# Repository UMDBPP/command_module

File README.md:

# ```</CMD>```

Command is the primary tracking payload flown by BPP. This repository contains design files and software required to run the current version of command.

Current POC:
Shipman

 ## Design Priciples
As the command module needs to fly on every flight mass reduction is a primary focus. For this reason a switch from perfboard to custom PCB's was done, and a substantial reduction in box volume is underway. Reliability is incredibly important and for this reason the payload operates its tracking systems in a full 4N redundant method.
### Tracking systems include (system/function):
#### 2x LiteAPRS 2m transmitters on 144.390 MHz
In flight position updates every minute. By nature of APRS tracking in hilly terrain unlikely to receive exact coordinates under 500m unless operating our own radios.
#### 1x SPOT Trace Tracker
COTS tracker from SPOT. Gives exact coordinates on landing.
#### 1x BITS (Balloon Iridium Telemetry System)
Exact coordinates throughout the flight, variable transmission rate 1min-15minutes (technically 10s-inf). Datalogger. XBee 900 HP allows for commands to be relayed through Iridium to other payloads and telemetry from payloads to be sent to ground. Possibility of ground to payload XBee communication without Iridium allowing for low latency high rate commanding.

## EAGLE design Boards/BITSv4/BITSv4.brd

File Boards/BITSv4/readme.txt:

Folder for BITSv4 development
Starting 10/3/2021,
jmolter

Work based on lessons from BITSv3

---Focus Areas---

-Reg LMR16020-
Keep the IC
Change inductor for easier assembly
Consider chaning output to 5v,
OR source 5v from another source

-Misc.-
Change power connector to match LightAPRS LVC

Change picoblade to right angle

Remove celltracker crosstalk conn

Consider GPS improvements

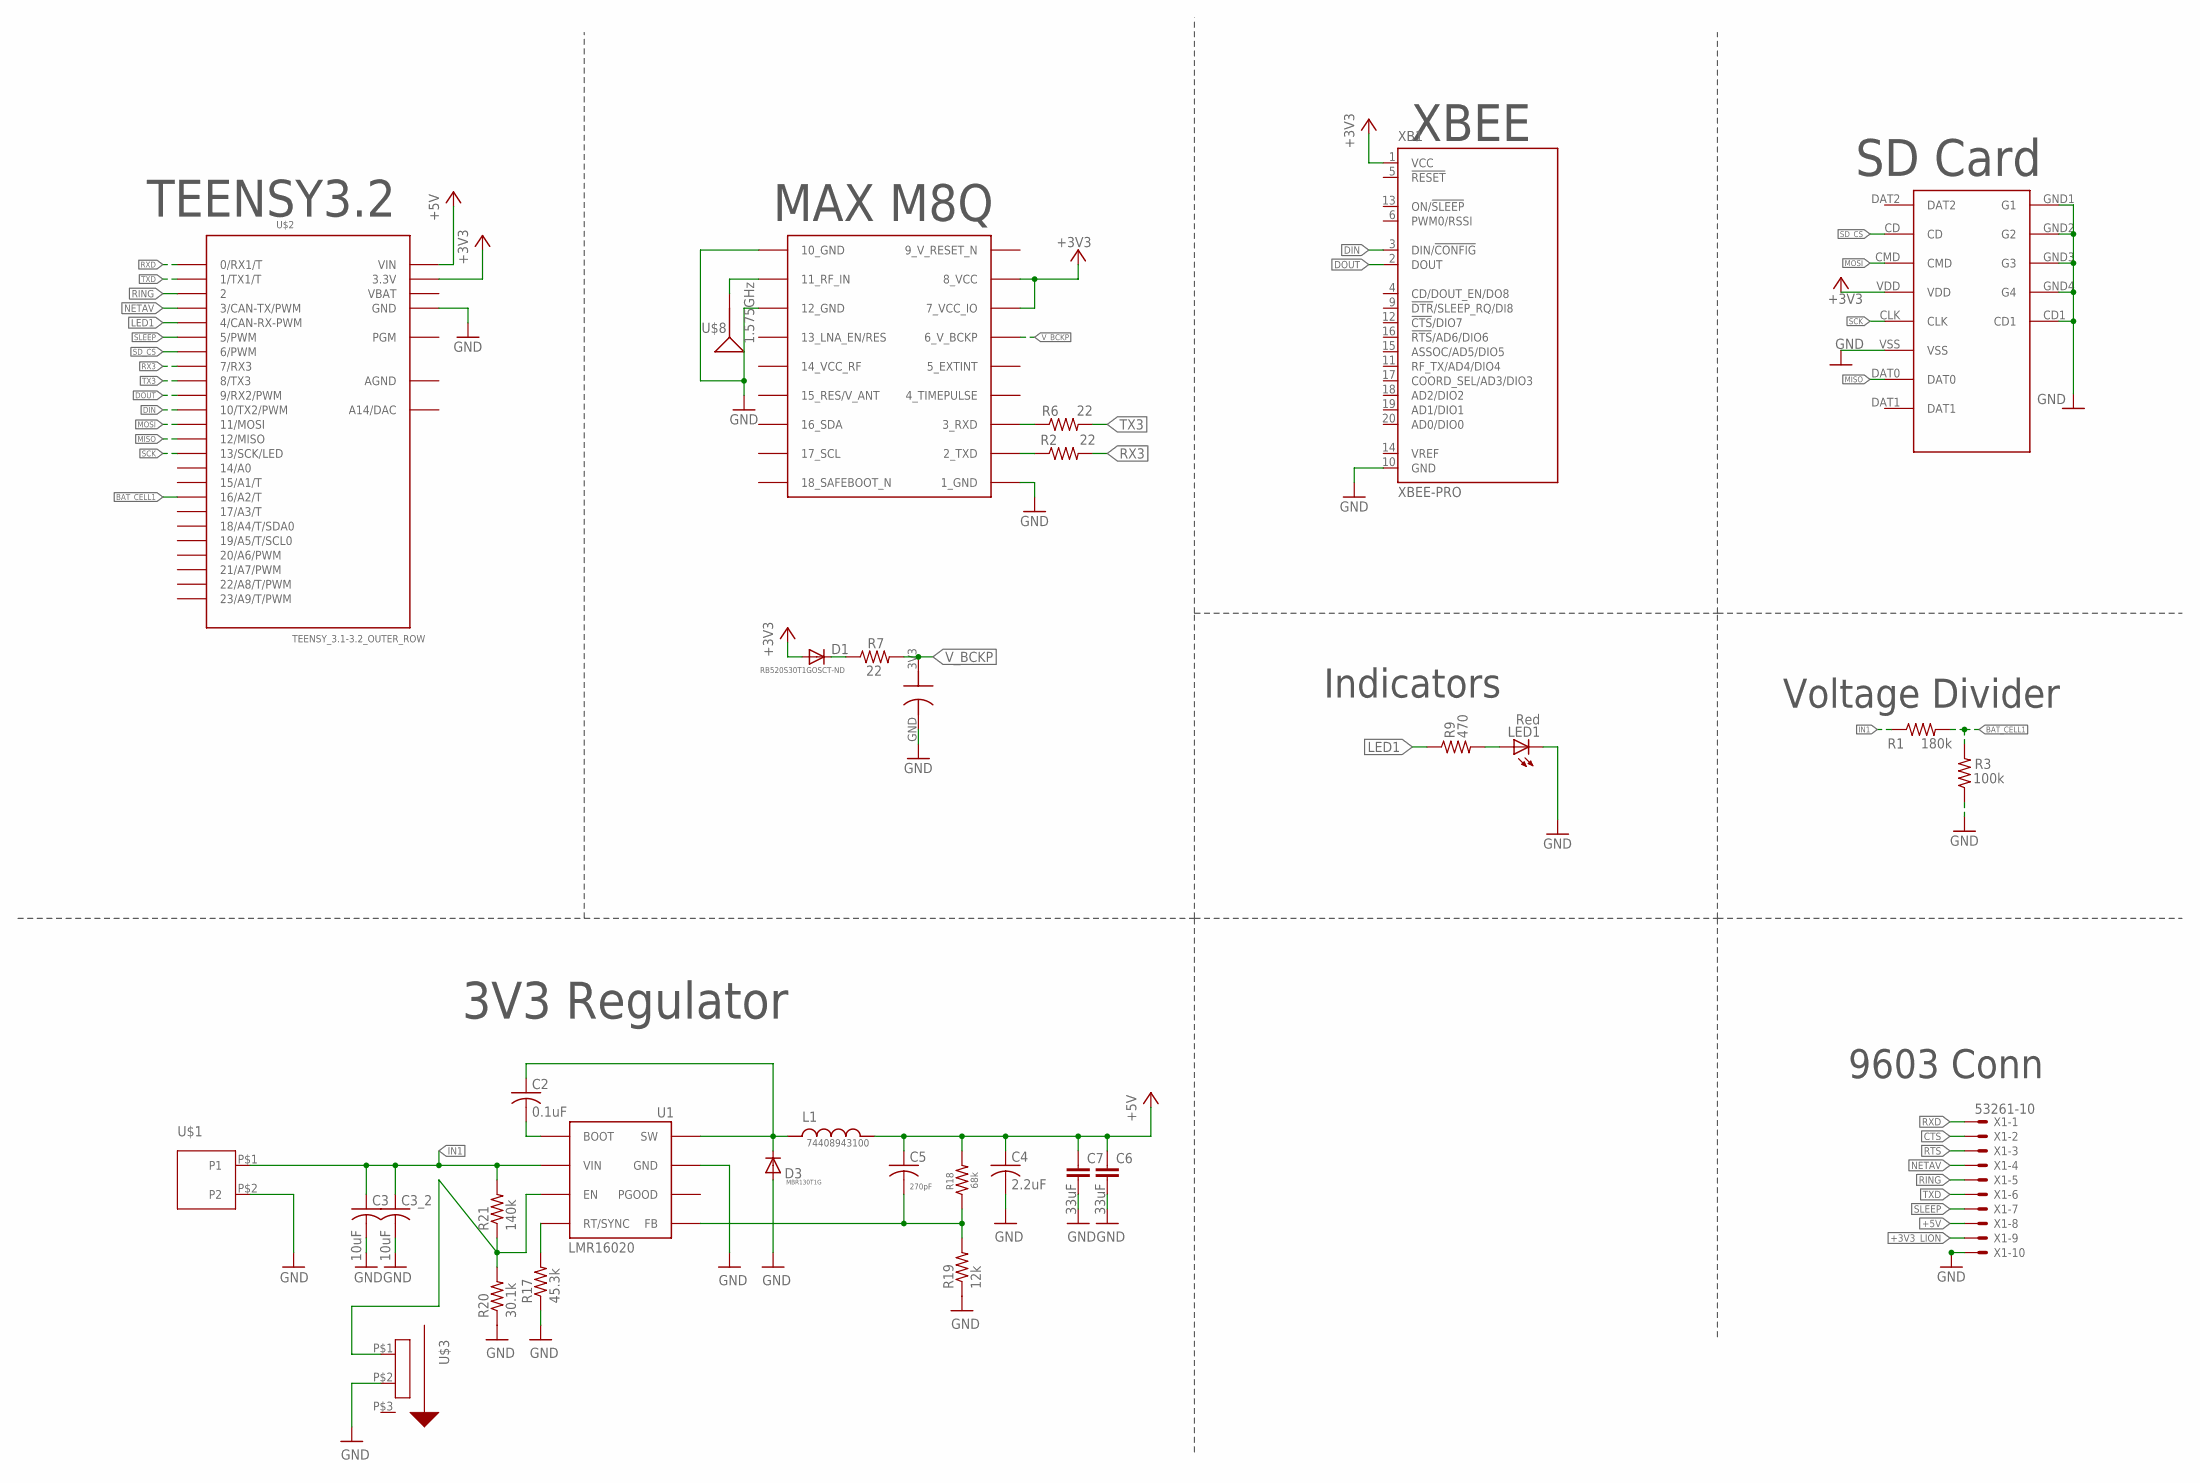
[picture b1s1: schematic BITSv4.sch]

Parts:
C1: 0.2F; ELNASUPERCAP
C2: 0.1uF; C0603
C3, C3_2: 10uF; C0805
C4: 2.2uF; C0603
C5: 270pF; C0402
C6, C7: 33uF; C050-024X044
D1: RB520S30T1GOSCT-ND; SOD523
D3: MBR130T1G; SOD-123_MINI-SMA
L1: 74408943100
LED1: Red; CHIP-LED0603
R1: 180k; R0603
R2, R6, R7: 22; R0603
R3: 100k; R0603
R9: 470; R0603
R17: 45.3k; R0603
R18: 68k; R0603
R19: 12k; R0603
R20: 30.1k; R0603
R21: 140k; R0603
U1: LMR16020; SO8
U$1: 559350210
U$2: TEENSY_3.1-3.2_OUTER_ROW; TEENSY_3.0-3.2&LC_OUTER_ROW
U$3: CL-SB-12B-01
U$4: MICRO_SD; MICRO_SD_HINGED
U$7: MAX-M8
U$8: 1.575GHz; SPARKFUN-GPS_ANT-GPS-2X7MM
X1: 53261-10
XB1: XBEE-PRO

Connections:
9_V_RESET_N: U$7.9_RESET_N (9_V_RESET_N)
+3V3: D1.A, U$2.3.3V, U$2.3.3V1 (3.3V), U$4.VDD, U$7.7_VCC_IO, U$7.8_VCC, XB1.1 (VCC)
+3V3_LION: X1.9
+5V: C4.1, C5.1, C6.1, C7.1, L1.P$2, R18.2, U$2.VIN, X1.8
AGND: U$2.AGND
BAT_CELL1: R1.2, R3.2, U$2.16/A2 (16/A2/T)
CTS: X1.2
DIN: U$2.10 (10/TX2/PWM), XB1.3 (DIN/!CONFIG)
DOUT: U$2.9 (9/RX2/PWM), XB1.2 (DOUT)
FB: C5.2, R18.1, R19.2, U1.P$5 (FB)
GND: C1.GND, C3.2, C3_2.2, C4.2, C6.2, C7.2, D3.A, LED1.C, R3.1, R17.1, R19.1, R20.1, U1.P$7 (GND), U1.PAD (GND), U$1.P$2 (P2), U$2.GND, U$2.GND1 (GND), U$3.P$2 (P2), U$4.CD1, U$4.GND1 (G1), U$4.GND2 (G2), U$4.GND3 (G3), U$4.GND4 (G4), U$4.VSS, U$7.1_GND, U$7.10_GND, U$7.12_GND, X1.10, XB1.10 (GND)
IN1: C3.1, C3_2.1, R1.1, R21.2, U1.P$2 (VIN), U$1.P$1 (P1)
LED1: R9.1, U$2.4 (4/CAN-RX-PWM)
MISO: U$2.12 (12/MISO), U$4.DAT0
MOSI: U$2.11 (11/MOSI), U$4.CMD
unnamed: U$7.11_RF_IN, U$8.1
unnamed: D1.C, R7.1
unnamed: R6.1, U$7.3_RXD
unnamed: R2.1, U$7.2_TXD
unnamed: LED1.A, R9.2
unnamed: R20.2, R21.1, U1.P$3 (EN), U$3.P$1 (P1)
unnamed: R17.2, U1.P$4 (RT/SYNC)
unnamed: C2.2, U1.P$1 (BOOT)
NETAV: U$2.3 (3/CAN-TX/PWM), X1.4
RING: U$2.2, X1.5
RTS: X1.3
RX3: R2.2, U$2.7 (7/RX3)
RXD: U$2.0 (0/RX1/T), X1.1
SCK: U$2.13 (13/SCK/LED), U$4.CLK
SD_CS: U$2.6 (6/PWM), U$4.CD
SLEEP: U$2.5 (5/PWM), X1.7
SW: C2.1, D3.C, L1.P$1, U1.P$8 (SW)
TX3: R6.2, U$2.8 (8/TX3)
TXD: U$2.1 (1/TX1/T), X1.6
VBAT: U$2.VBAT
V_BCKP: C1.3V3, R7.2, U$7.6_V_BCKP

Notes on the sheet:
MAX M8Q
TEENSY3.2
Voltage Divider
Indicators
SD Card
9603 Conn
3V3 Regulator
XBEE

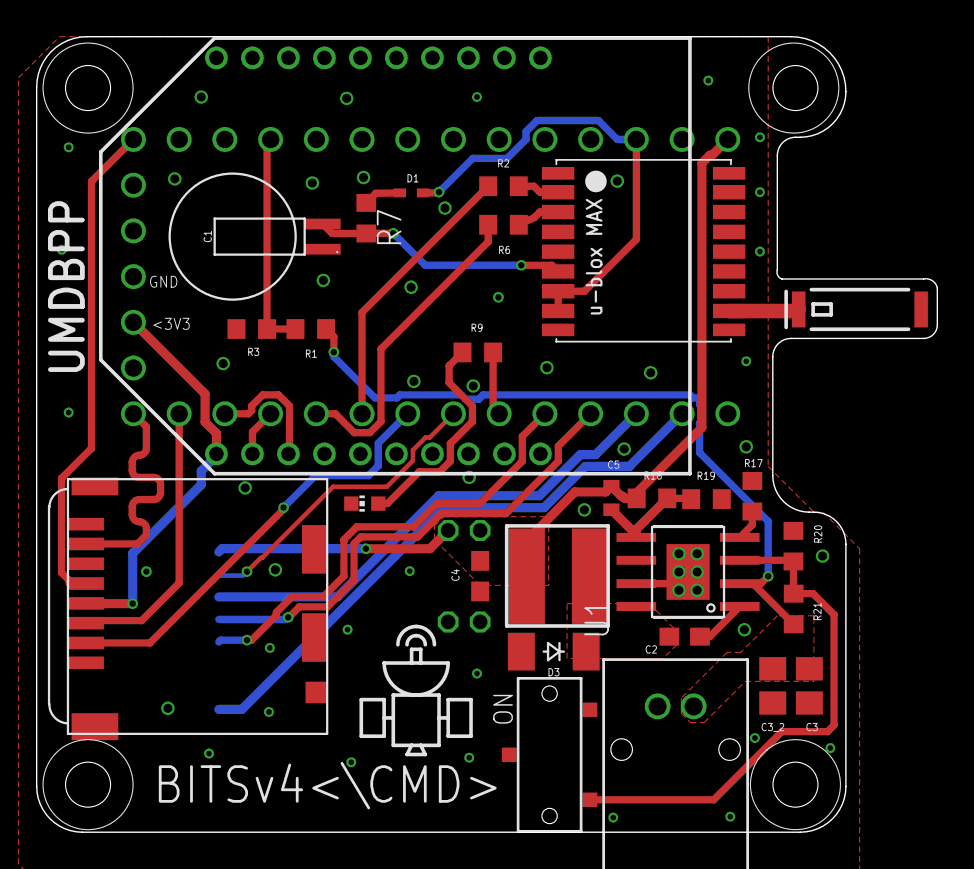
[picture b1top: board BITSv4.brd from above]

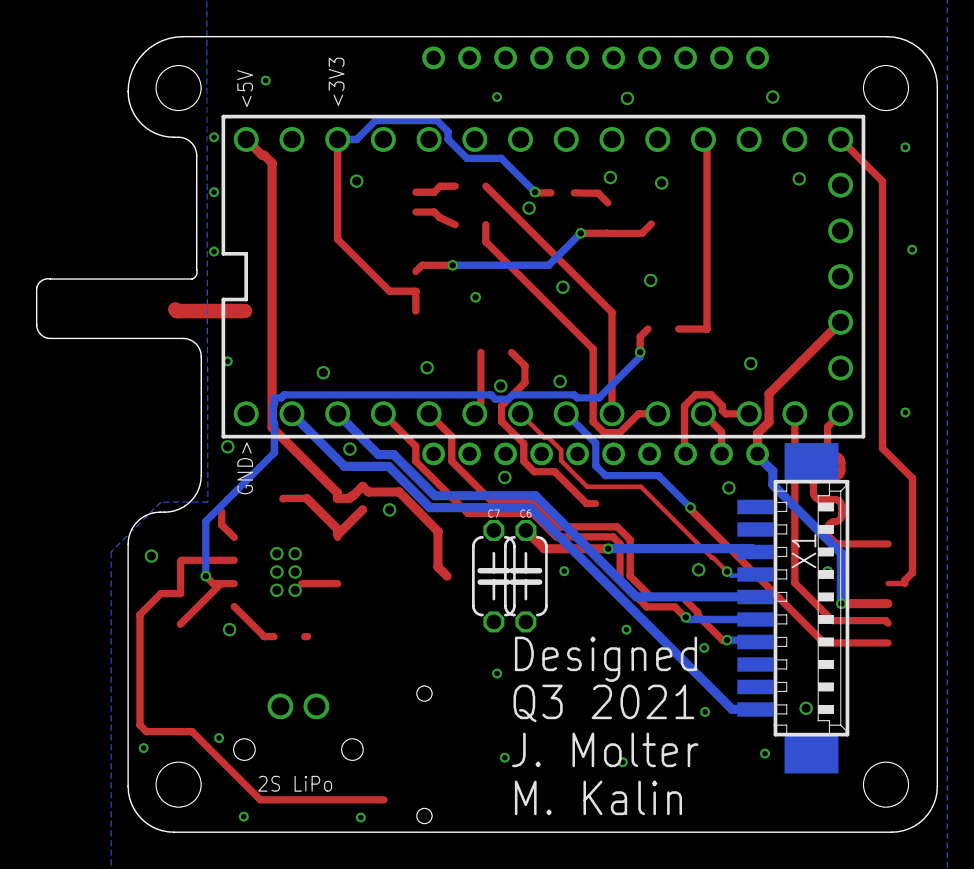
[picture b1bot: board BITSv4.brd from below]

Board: 2 copper layers, 50.0 x 44.2 mm, 32 parts (4 on the bottom side), 30 nets.

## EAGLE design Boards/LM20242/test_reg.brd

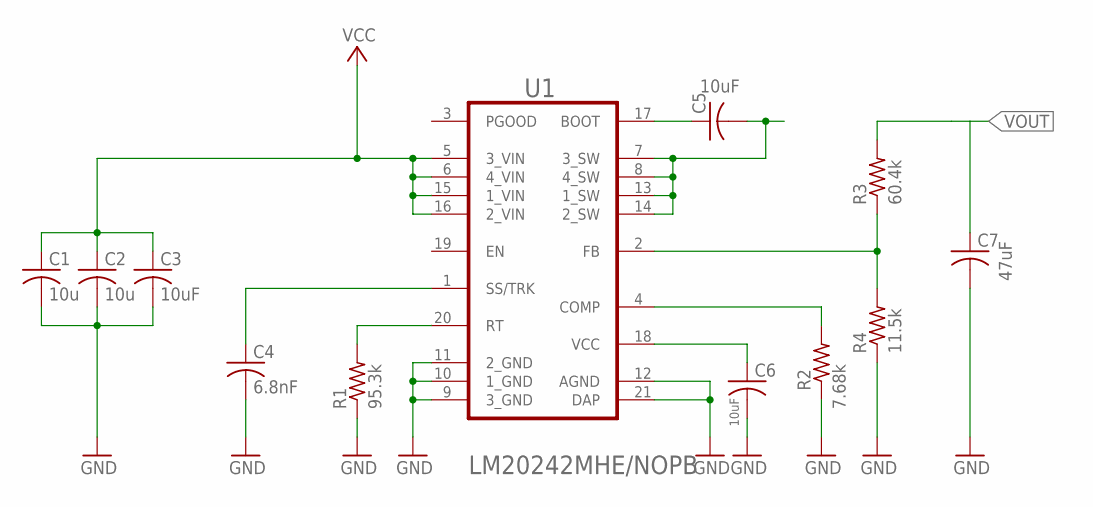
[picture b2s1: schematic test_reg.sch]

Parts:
C1, C2: 10u; C0805
C3, C5, C6: 10uF; C0805
C4: 6.8nF; C0805
C7: 47uF; C0805
R1: 95.3k; R0805
R2: 7.68k; R0805
R3: 60.4k; R0805
R4: 11.5k; R0805
U1: TI_NATIONAL_SEMICONDUCTOR_LM20242MHE-NOPBTI_NATIO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; TI_NATIONAL_SEMICONDUCTOR_LM20242MHE-NOPB_0

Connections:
GND: C1.2, C2.2, C3.2, C4.2, C6.2, C7.2, R1.1, R2.1, R4.1, U1.9 (3_GND), U1.10 (1_GND), U1.11 (2_GND), U1.12 (AGND), U1.21 (DAP)
unnamed: R1.2, U1.20 (RT)
unnamed: R2.2, U1.4 (COMP)
unnamed: C4.1, U1.1 (SS/TRK)
unnamed: C5.2, U1.7 (3_SW), U1.8 (4_SW), U1.13 (1_SW), U1.14 (2_SW)
unnamed: C5.1, U1.17 (BOOT)
unnamed: R3.1, R4.2, U1.2 (FB)
unnamed: C6.1, U1.18 (VCC)
VCC: C1.1, C2.1, C3.1, U1.5 (3_VIN), U1.6 (4_VIN), U1.15 (1_VIN), U1.16 (2_VIN)
VOUT: C7.1, R3.2

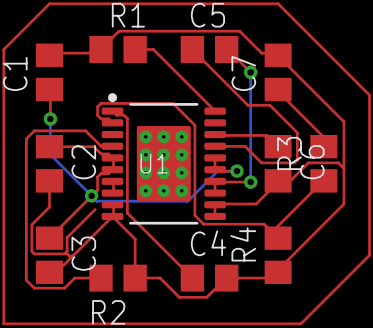
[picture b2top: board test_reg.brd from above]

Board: 2 copper layers, 12 parts (0 on the bottom side), 10 nets.

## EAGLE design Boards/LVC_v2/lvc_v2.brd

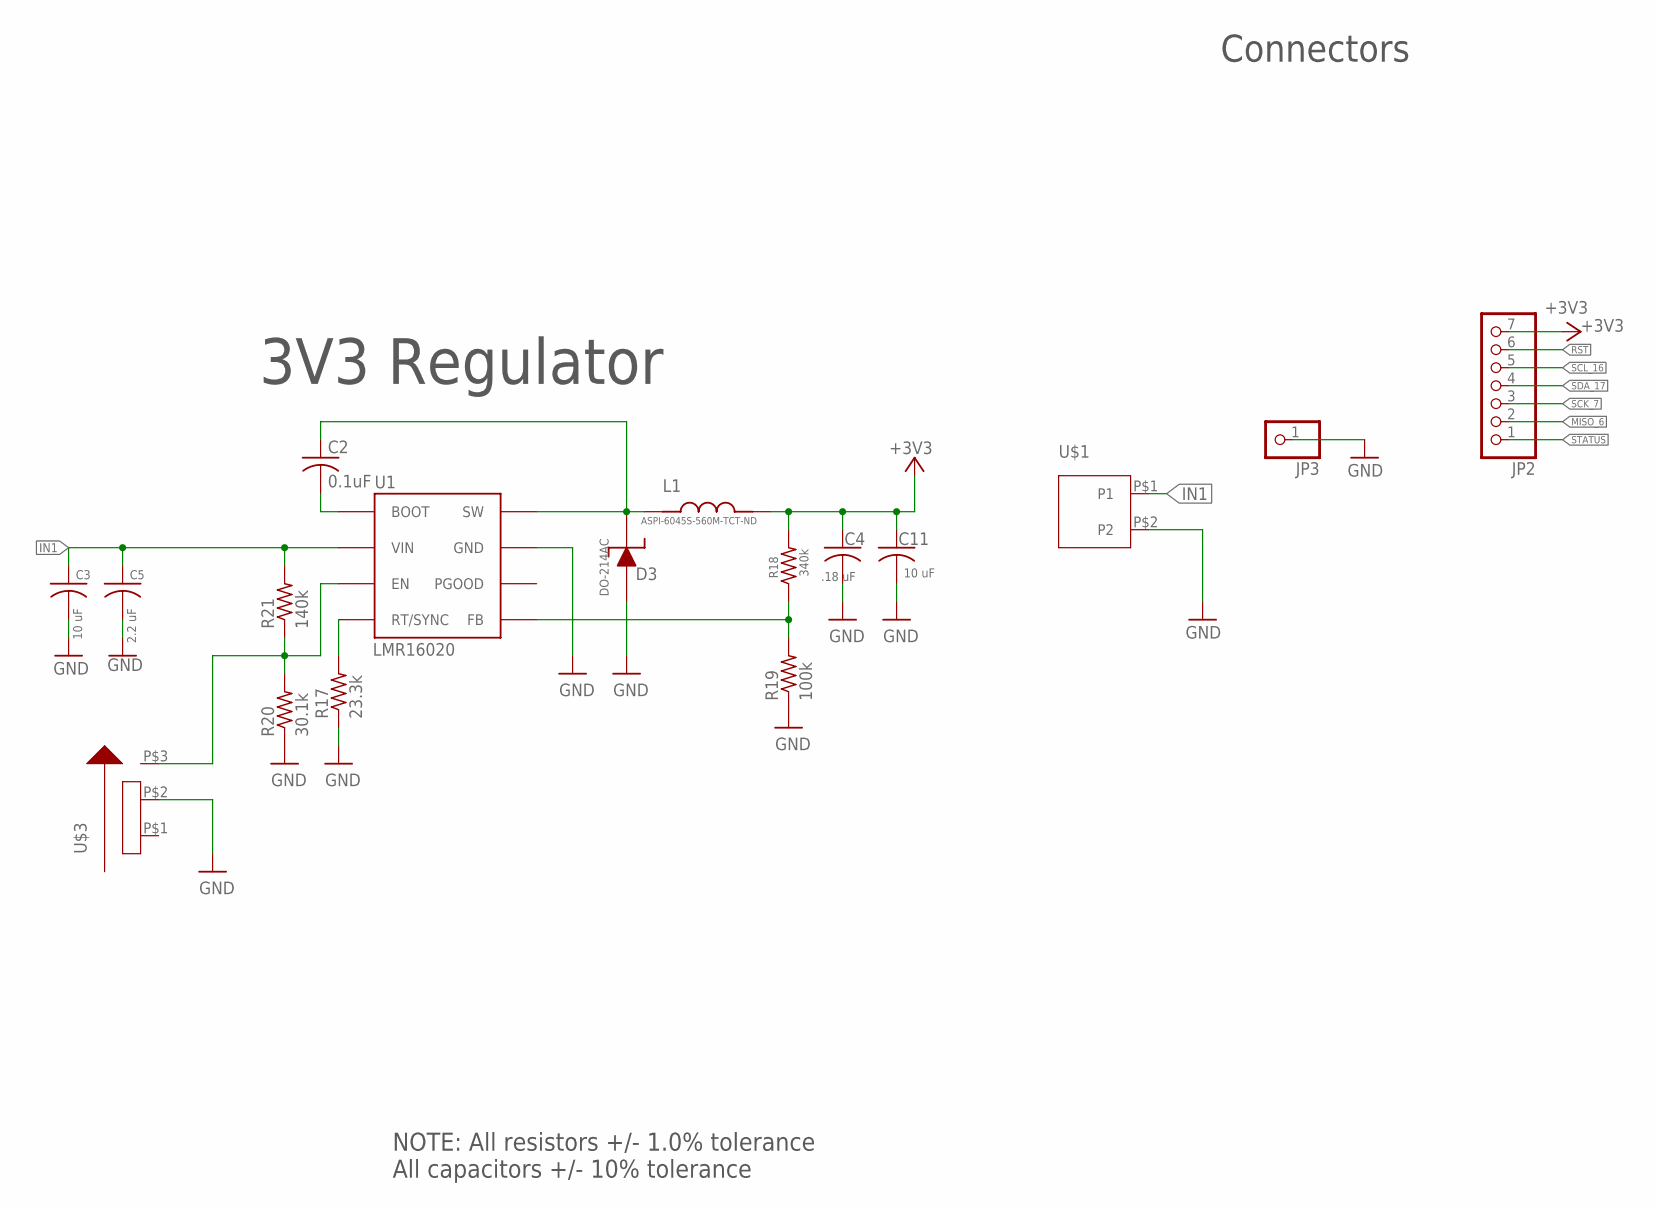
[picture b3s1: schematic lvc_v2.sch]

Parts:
C2: 0.1uF; C0603
C3: 10 uF; C1210
C4: .18 uF; C0603
C5: 2.2 uF; C1210
C11: 10 uF; C0603
D3: DO-214AC
JP2: PINHD-1X7; 1X07
JP3: PINHD-1X1; 1X01
L1: ASPI-6045S-560M-TCT-ND; ABRACON
R17: 23.3k; R0603
R18: 340k; R0603
R19: 100k; R0603
R20: 30.1k; R0603
R21: 140k; R0603
U1: LMR16020; SO8
U$1: 559350210
U$3: CL-SB-12B-01

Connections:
+3V3: C4.1, C11.1, JP2.7, L1.P$2, R18.2
FB: R18.1, R19.2, U1.P$5 (FB)
GND: C3.2, C4.2, C5.2, C11.2, D3.P$1, JP3.1, R17.1, R19.1, R20.1, U1.P$7 (GND), U1.PAD (GND), U$1.P$2 (P2), U$3.P$2 (P2)
IN1: C3.1, C5.1, R21.2, U1.P$2 (VIN), U$1.P$1 (P1)
MISO_6: JP2.2
unnamed: R20.2, R21.1, U1.P$3 (EN), U$3.P$3 (P3)
unnamed: R17.2, U1.P$4 (RT/SYNC)
unnamed: C2.2, U1.P$1 (BOOT)
RST: JP2.6
SCK_7: JP2.3
SCL_16: JP2.5
SDA_17: JP2.4
STATUS: JP2.1
SW: C2.1, D3.P$2, L1.P$1, U1.P$8 (SW)

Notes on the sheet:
Connectors
NOTE: All resistors +/- 1.0% tolerance All capacitors +/- 10% tolerance
3V3 Regulator

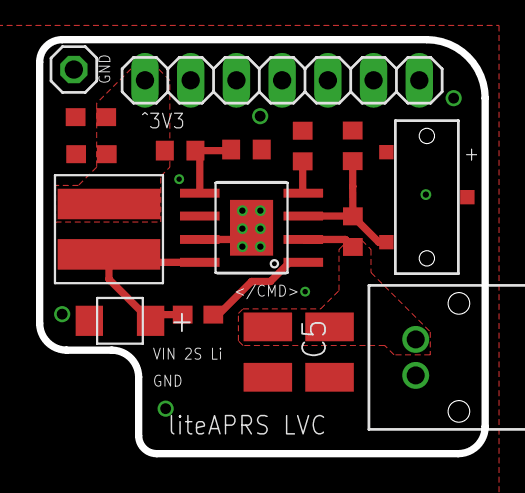
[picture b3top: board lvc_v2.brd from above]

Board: 2 copper layers, 24.8 x 23.0 mm, 17 parts (0 on the bottom side), 8 nets.

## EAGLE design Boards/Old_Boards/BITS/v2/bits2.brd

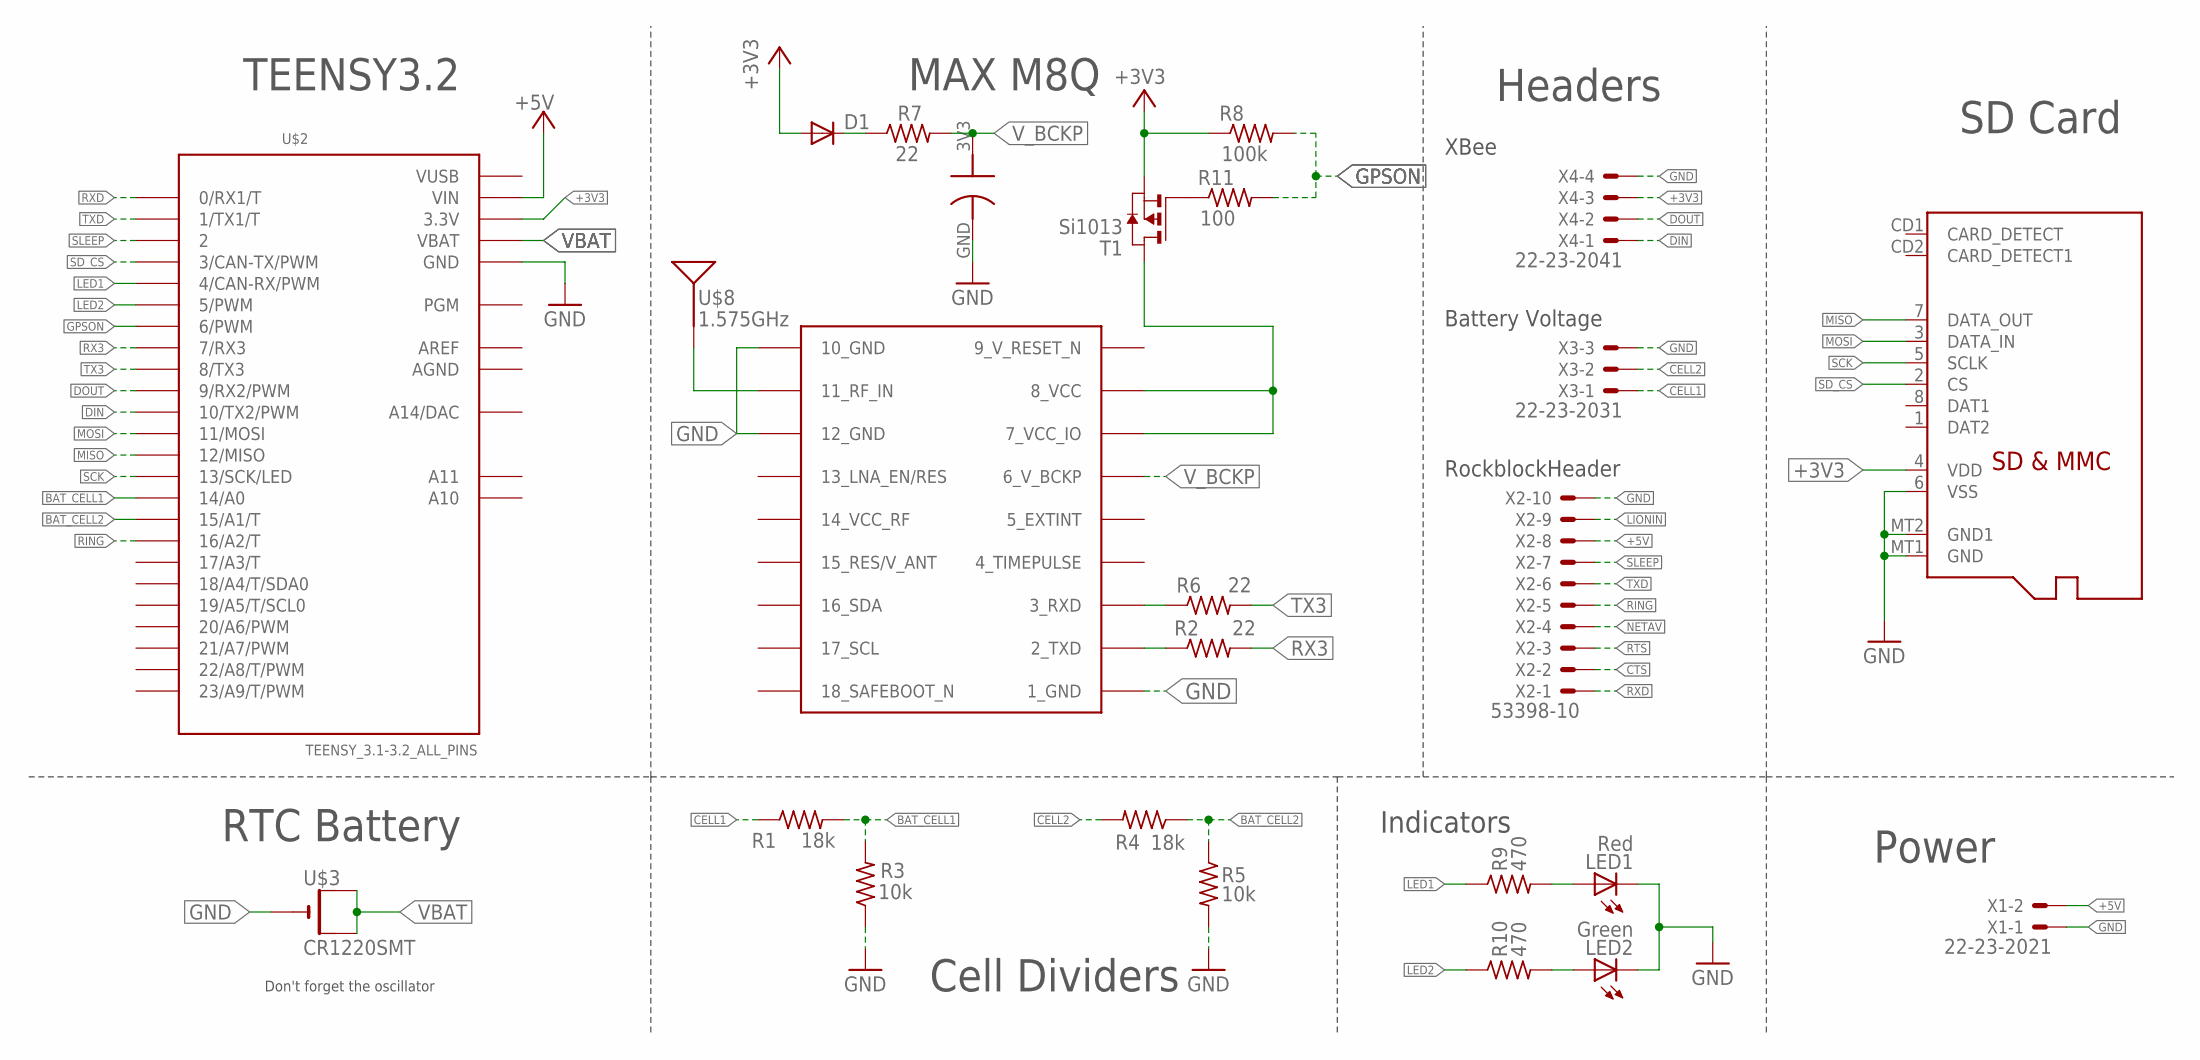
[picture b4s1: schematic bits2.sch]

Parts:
C1: DCK-3R3E204T614-E; ELNASUPERCAP
D1: DIODE-SOD523; SOD523
LED1: Red; CHIP-LED0603
LED2: Green; CHIP-LED0603
R1, R4: 18k; R0603
R2, R6, R7: 22; R0603
R3, R5: 10k; R0603
R8: 100k; R0603
R9, R10: 470; R0603
R11: 100; R0603
T1: Si1013; SOT-23
U$1: MICROSD
U$2: TEENSY_3.1-3.2_ALL_PINS; TEENSY_3.0-3.2&LC_ALL_PINS
U$3: CR1220SMT; CR1220-SMD
U$7: MAX-M8
U$8: 1.575GHz; SPARKFUN-GPS_ANT-GPS-2X7MM
X1: 22-23-2021
X2: 53398-10
X3: 22-23-2031
X4: 22-23-2041

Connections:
9_V_RESET_N: U$7.9_RESET_N (9_V_RESET_N)
+3V3: D1.A, R8.1, T1.2 (S), U$1.4 (VDD), U$2.3.3V, U$2.3.3V1 (3.3V), X4.3
+5V: U$2.VIN, X1.2, X2.8
AGND: U$2.AGND
AREF: U$2.AREF
BAT_CELL1: R1.2, R3.2, U$2.14/A0
BAT_CELL2: R4.1, R5.1, U$2.15/A1 (15/A1/T)
CELL1: R1.1, X3.1
CELL2: R4.2, X3.2
CTS: X2.2
DIN: U$2.10 (10/TX2/PWM), X4.1
DOUT: U$2.9 (9/RX2/PWM), X4.2
GND: C1.GND, LED1.C, LED2.C, R3.1, R5.2, U$1.6 (VSS), U$1.MT1 (GND), U$1.MT2 (GND1), U$2.GND, U$2.GND1 (GND), U$3.-, U$7.1_GND, U$7.10_GND, U$7.12_GND, X1.1, X2.10, X3.3, X4.4
GPSON: R8.2, R11.2, U$2.6 (6/PWM)
LED1: R9.1, U$2.4 (4/CAN-RX/PWM)
LED2: R10.1, U$2.5 (5/PWM)
LIONIN: X2.9
MISO: U$1.7 (DATA_OUT), U$2.12 (12/MISO)
MOSI: U$1.3 (DATA_IN), U$2.11 (11/MOSI)
unnamed: U$7.11_RF_IN, U$8.1
unnamed: D1.C, R7.1
unnamed: R6.1, U$7.3_RXD
unnamed: R2.1, U$7.2_TXD
unnamed: LED2.A, R10.2
unnamed: LED1.A, R9.2
unnamed: R11.1, T1.3 (G)
unnamed: T1.1 (D), U$7.7_VCC_IO, U$7.8_VCC
NETAV: X2.4
RING: U$2.16/A2 (16/A2/T), X2.5
RTS: X2.3
RX3: R2.2, U$2.7 (7/RX3)
RXD: U$2.0 (0/RX1/T), X2.1
SCK: U$1.5 (SCLK), U$2.13 (13/SCK/LED)
SD_CS: U$1.2 (CS), U$2.3 (3/CAN-TX/PWM)
SLEEP: U$2.2, X2.7
TX3: R6.2, U$2.8 (8/TX3)
TXD: U$2.1 (1/TX1/T), X2.6
VBAT: U$2.VBAT, U$3.+$1 (+), U$3.+$2 (+1)
VUSB: U$2.VUSB
V_BCKP: C1.3V3, R7.2, U$7.6_V_BCKP

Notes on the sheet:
MAX M8Q
TEENSY3.2
RTC Battery
Cell Dividers
Indicators
Power
Headers
SD Card
Don't forget the oscillator
RockblockHeader
Battery Voltage
XBee

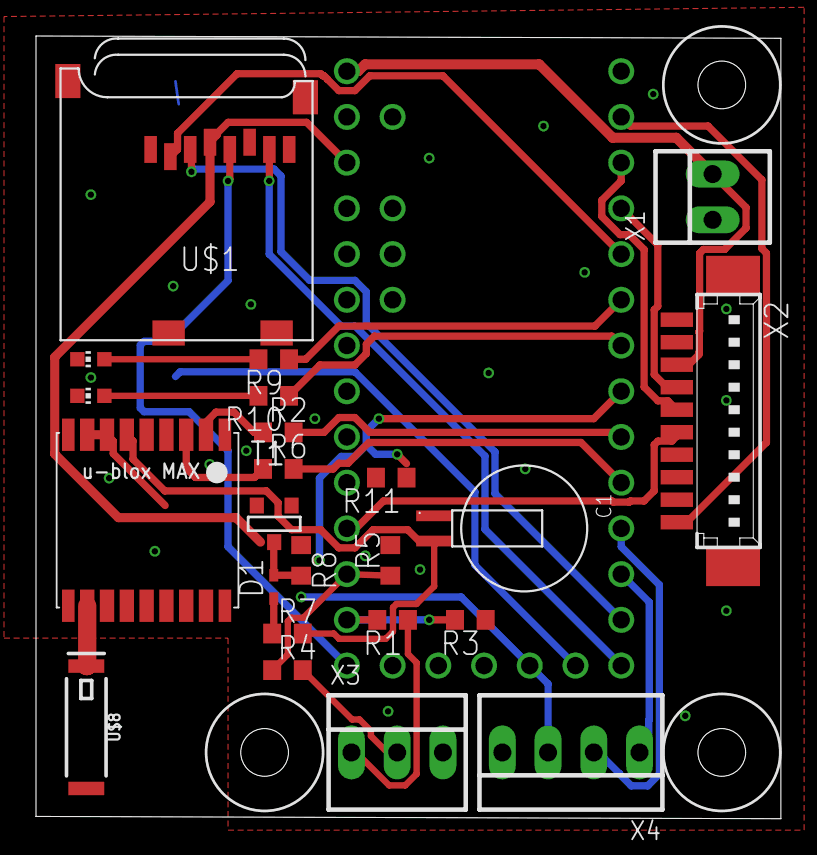
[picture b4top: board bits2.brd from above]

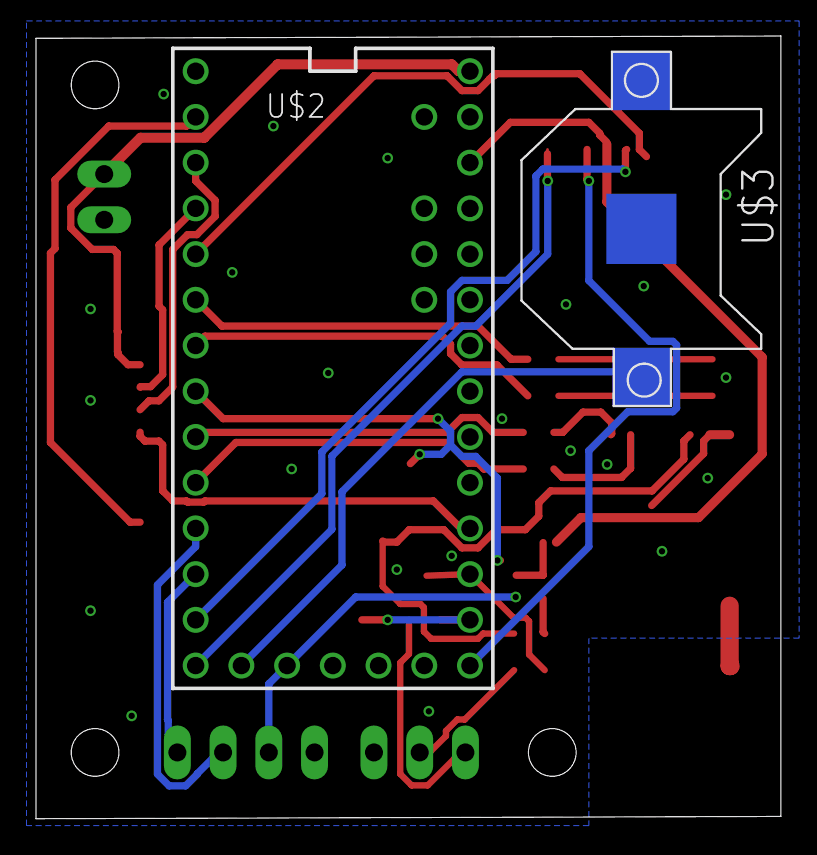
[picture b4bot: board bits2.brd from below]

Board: 2 copper layers, 41.4 x 43.5 mm, 25 parts (2 on the bottom side), 32 nets.

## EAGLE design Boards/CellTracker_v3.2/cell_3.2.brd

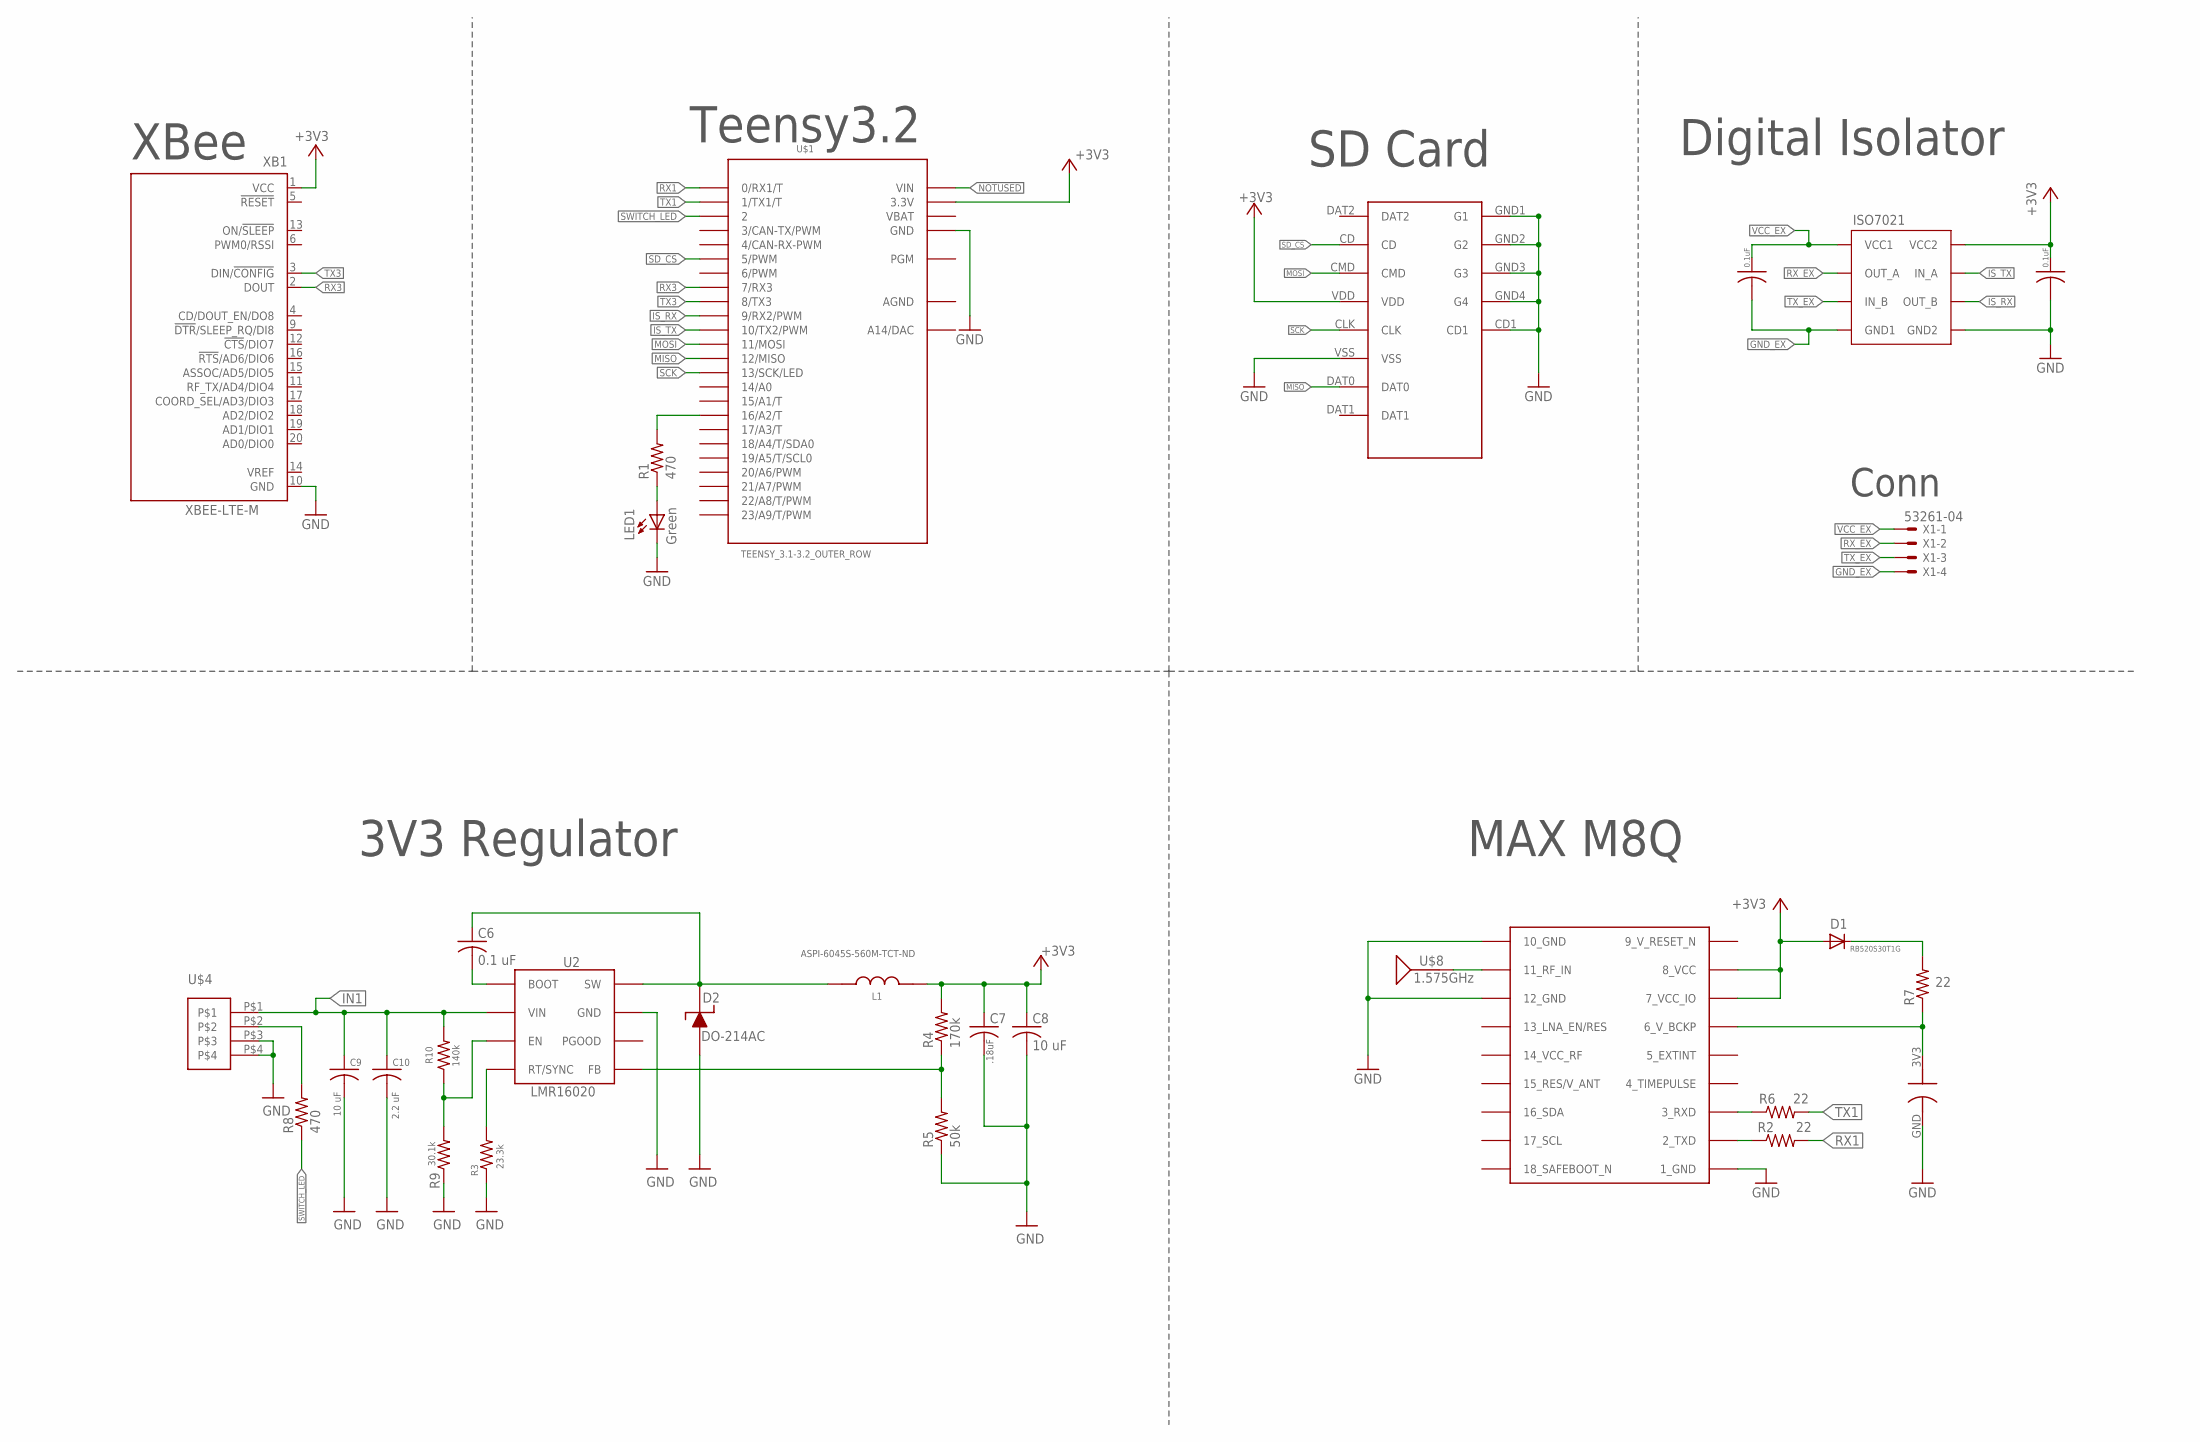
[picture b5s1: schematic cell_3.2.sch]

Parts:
C1: 0.3F; ELNASUPERCAP
C2, C3: 0.1uF; C0603
C6: 0.1 uF; C0805
C7: .18uF; C0603
C8: 10 uF; C0603
C9: 10 uF; C1210
C10: 2.2 uF; C1210
D1: RB520S30T1G; SOD523
D2: DO-214AC
ISO7021: ISO7021; 8-SOIC
L1: ASPI-6045S-560M-TCT-ND; ABRACON
LED1: Green; CHIP-LED0603
R1, R8: 470; R0603
R2, R6, R7: 22; R0603
R3: 23.3k; R0603
R4: 170k; R0603
R5: 50k; R0603
R9: 30.1k; R0603
R10: 140k; R0603
U2: LMR16020; SO8
U$1: TEENSY_3.1-3.2_OUTER_ROW; TEENSY_3.0-3.2&LC_OUTER_ROW
U$3: MICRO_SD; MICRO_SD_HINGED
U$4: MICROCLASP_4; 4_PIN_MICROCLASP
U$7: MAX-M8
U$8: 1.575GHz; SPARKFUN-GPS_ANT-GPS-2X7MM
X1: 53261-04
XB1: XBEE-LTE-M; XBEE-PRO

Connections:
9_V_RESET_N: U$7.9_RESET_N (9_V_RESET_N)
+3V3: C3.1, C7.1, C8.1, D1.A, ISO7021.P$8 (VCC2), L1.P$2, R4.2, U$1.3.3V, U$1.3.3V1 (3.3V), U$3.VDD, U$7.7_VCC_IO, U$7.8_VCC, XB1.1 (VCC)
AGND: U$1.AGND
EN: R9.2, R10.1, U2.P$3 (EN)
FB: R4.1, R5.2, U2.P$5 (FB)
GND: C1.GND, C3.2, C7.2, C8.2, C9.2, C10.2, D2.P$1, ISO7021.P$5 (GND2), LED1.C, R3.1, R5.1, R9.1, U2.P$7 (GND), U2.PAD (GND), U$1.GND, U$1.GND1 (GND), U$3.CD1, U$3.GND1 (G1), U$3.GND2 (G2), U$3.GND3 (G3), U$3.GND4 (G4), U$3.VSS, U$4.P$3, U$4.P$4, U$7.1_GND, U$7.10_GND, U$7.12_GND, XB1.10 (GND)
GND_EX: C2.2, ISO7021.P$4 (GND1), X1.4
IN1: C9.1, C10.1, R10.2, U2.P$2 (VIN), U$4.P$1
IS_RX: ISO7021.P$6 (OUT_B), U$1.9 (9/RX2/PWM)
IS_TX: ISO7021.P$7 (IN_A), U$1.10 (10/TX2/PWM)
MISO: U$1.12 (12/MISO), U$3.DAT0
MOSI: U$1.11 (11/MOSI), U$3.CMD
unnamed: U$7.11_RF_IN, U$8.1
unnamed: R1.2, U$1.16/A2 (16/A2/T)
unnamed: R6.1, U$7.3_RXD
unnamed: R2.1, U$7.2_TXD
unnamed: C1.3V3, R7.1, U$7.6_V_BCKP
unnamed: D1.C, R7.2
unnamed: R3.2, U2.P$4 (RT/SYNC)
unnamed: C6.2, U2.P$1 (BOOT)
unnamed: LED1.A, R1.1
unnamed: R8.2, U$4.P$2
NOTUSED: U$1.VIN
RX1: R2.2, U$1.0 (0/RX1/T)
RX3: U$1.7 (7/RX3), XB1.2 (DOUT)
RX_EX: ISO7021.P$2 (OUT_A), X1.2
SCK: U$1.13 (13/SCK/LED), U$3.CLK
SD_CS: U$1.5 (5/PWM), U$3.CD
SW: C6.1, D2.P$2, L1.P$1, U2.P$8 (SW)
SWITCH_LED: R8.1, U$1.2
TX1: R6.2, U$1.1 (1/TX1/T)
TX3: U$1.8 (8/TX3), XB1.3 (DIN/!CONFIG)
TX_EX: ISO7021.P$3 (IN_B), X1.3
VBAT: U$1.VBAT
VCC_EX: C2.1, ISO7021.P$1 (VCC1), X1.1

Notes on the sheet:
MAX M8Q
SD Card
XBee
Teensy3.2
3V3 Regulator
Digital Isolator
Conn

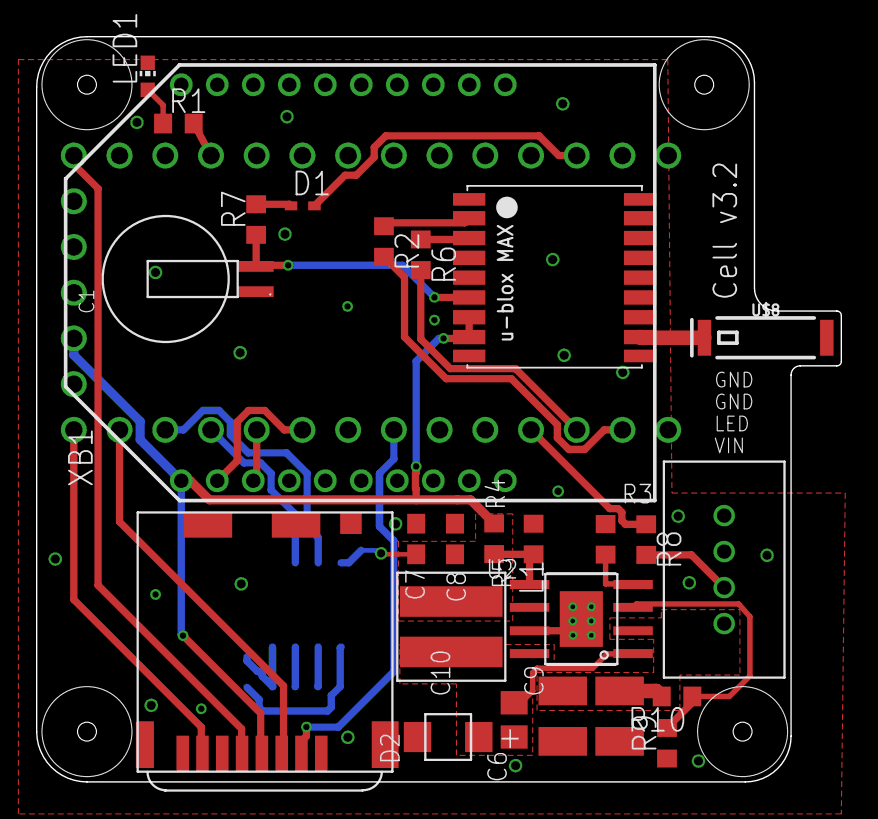
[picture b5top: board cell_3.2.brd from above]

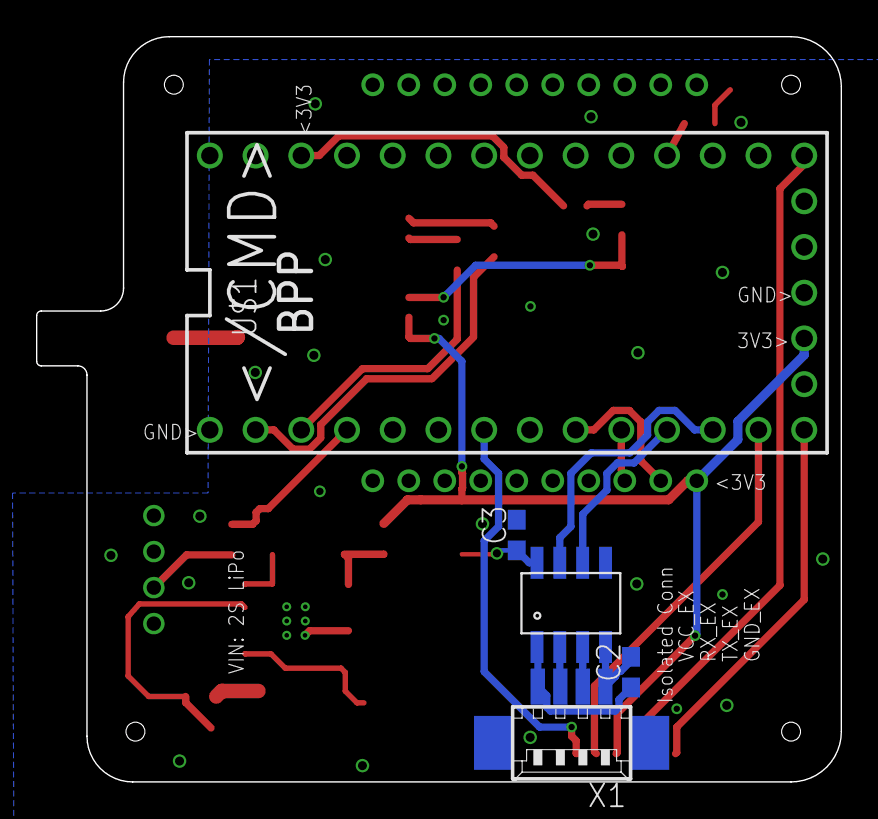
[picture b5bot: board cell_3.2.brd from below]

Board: 2 copper layers, 44.7 x 41.4 mm, 31 parts (5 on the bottom side), 31 nets.
